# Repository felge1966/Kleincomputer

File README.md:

# Projekte um die DDR Kleincomputer 
- KC85/2...85/5
- Z9001, KC85/1 und KC87 
- MRB Z1013
- AC1 (org / AC1-2010 / Neubauprojekt AC1-2017 /AC1Pico)
- Polycomputer Poly880
- LC80 (LC80 org. / LC80ex)

## Dev Software:
 - WinCupl
 - Kicad 5.1

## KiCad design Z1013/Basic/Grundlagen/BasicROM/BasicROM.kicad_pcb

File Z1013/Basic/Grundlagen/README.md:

# Z1013-Basic
Platinenprojekt Z1013 Basicerweiterung

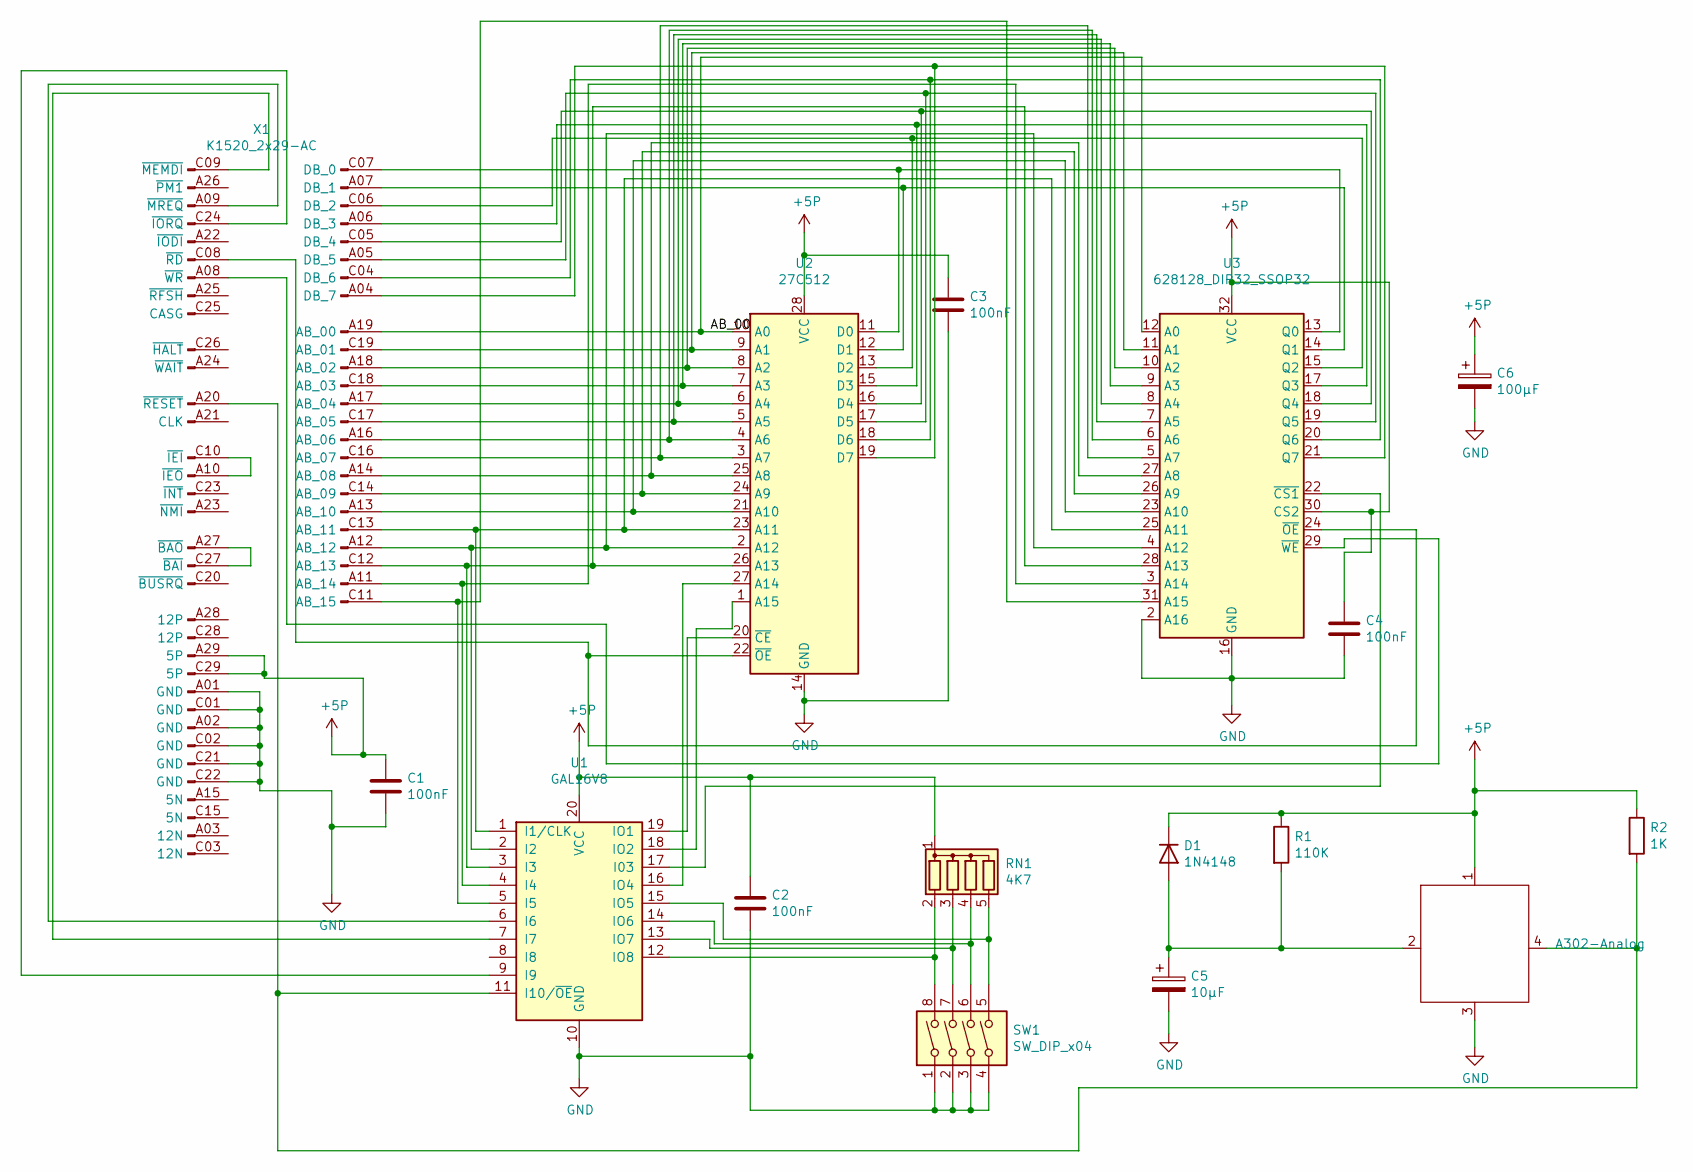
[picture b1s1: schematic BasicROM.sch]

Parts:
C1, C2, C3, C4: 100nF; C_Axial_L3.8mm_D2.6mm_P10.00mm_Horizontal
C5: 10µF; CP_Radial_D6.3mm_P2.50mm
C6: 100µF; CP_Axial_L18.0mm_D8.0mm_P25.00mm_Horizontal
D1: 1N4148; D_DO-35_SOD27_P7.62mm_Horizontal
R1: 110K; R_Axial_DIN0207_L6.3mm_D2.5mm_P7.62mm_Horizontal
R2: 1K; R_Axial_DIN0207_L6.3mm_D2.5mm_P7.62mm_Horizontal
RN1: 4K7; R_Array_SIP5
SW1: SW_DIP_x04; SW_DIP_SPSTx04_Piano_10.8x11.72mm_W7.62mm_P2.54mm
U1: GAL16V8; DIP-20_W7.62mm
U2: 27C512; DIP-28_W15.24mm
U3: 628128_DIP32_SSOP32; DIP-32_W15.24mm
U4: A302-Analog; DIP-4_W7.62mm
X1: K1520_2x29-AC; K1520_EFS2x29_DIN_male

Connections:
+5P: C1.1, C2.1, C3.1, C4.1, C6.1, D1.1 (K), R1.1, R2.1, RN1.1 (common), U1.20 (VCC), U2.28 (VCC), U3.30 (CS2), U3.32 (VCC), U4.1, X1.A29 (5P), X1.C29 (5P)
/AB_00: U2.10 (A0), U3.12 (A0), X1.A19 (AB_00)
GND: C1.2, C2.2, C3.2, C4.2, C5.2, C6.2, SW1.1, SW1.2, SW1.3, SW1.4, U1.10 (GND), U2.14 (GND), U3.2 (A16), U3.16 (GND), U4.3, X1.A01 (GND), X1.A02 (GND), X1.C01 (GND), X1.C02 (GND), X1.C21 (GND), X1.C22 (GND)
unnamed: C5.1, D1.2 (A), R1.2, U4.2
unnamed: R2.2, U1.11 (I10/~OE~), U4.4, X1.A20 (~RESET)
unnamed: RN1.2 (R1), SW1.8, U1.12 (IO8)
unnamed: RN1.3 (R2), SW1.7, U1.13 (IO7)
unnamed: RN1.4 (R3), SW1.6, U1.14 (IO6)
unnamed: RN1.5 (R4), SW1.5, U1.15 (IO5)
unnamed: U1.1 (I1/CLK), U2.23 (A11), U3.25 (A11), X1.C13 (AB_11)
unnamed: U1.2 (I2), U2.2 (A12), U3.4 (A12), X1.A12 (AB_12)
unnamed: U1.3 (I3), U2.26 (A13), U3.28 (A13), X1.C12 (AB_13)
unnamed: U1.4 (I4), U3.3 (A14), X1.A11 (AB_14)
unnamed: U1.5 (I5), U3.31 (A15), X1.C11 (AB_15)
unnamed: U1.6 (I6), X1.A09 (~MREQ)
unnamed: U1.7 (I7), X1.C09 (~MEMDI)
unnamed: U1.9 (I9), X1.C24 (~IORQ)
unnamed: U1.16 (IO4), U2.27 (A14)
unnamed: U1.17 (I03), U3.22 (~CS1)
unnamed: U1.18 (IO2), U2.1 (A15)
unnamed: U1.19 (IO1), U2.20 (~CE)
unnamed: U2.3 (A7), U3.5 (A7), X1.C16 (AB_07)
unnamed: U2.4 (A6), U3.6 (A6), X1.A16 (AB_06)
unnamed: U2.5 (A5), U3.7 (A5), X1.C17 (AB_05)
unnamed: U2.6 (A4), U3.8 (A4), X1.A17 (AB_04)
unnamed: U2.7 (A3), U3.9 (A3), X1.C18 (AB_03)
unnamed: U2.8 (A2), U3.10 (A2), X1.A18 (AB_02)
unnamed: U2.9 (A1), U3.11 (A1), X1.C19 (AB_01)
unnamed: U2.11 (D0), U3.13 (Q0), X1.C07 (DB_0)
unnamed: U2.12 (D1), U3.14 (Q1), X1.A07 (DB_1)
unnamed: U2.13 (D2), U3.15 (Q2), X1.C06 (DB_2)
unnamed: U2.15 (D3), U3.17 (Q3), X1.A06 (DB_3)
unnamed: U2.16 (D4), U3.18 (Q4), X1.C05 (DB_4)
unnamed: U2.17 (D5), U3.19 (Q5), X1.A05 (DB_5)
unnamed: U2.18 (D6), U3.20 (Q6), X1.C04 (DB_6)
unnamed: U2.19 (D7), U3.21 (Q7), X1.A04 (DB_7)
unnamed: U2.21 (A10), U3.23 (A10), X1.A13 (AB_10)
unnamed: U2.22 (~OE), U3.24 (~OE), X1.C08 (~RD)
unnamed: U2.24 (A9), U3.26 (A9), X1.C14 (AB_09)
unnamed: U2.25 (A8), U3.27 (A8), X1.A14 (AB_08)
unnamed: U3.29 (~WE), X1.A08 (~WR)
unnamed: X1.A10 (~IEO), X1.C10 (~IEI)
unnamed: X1.A27 (~BAO), X1.C27 (~BAI)

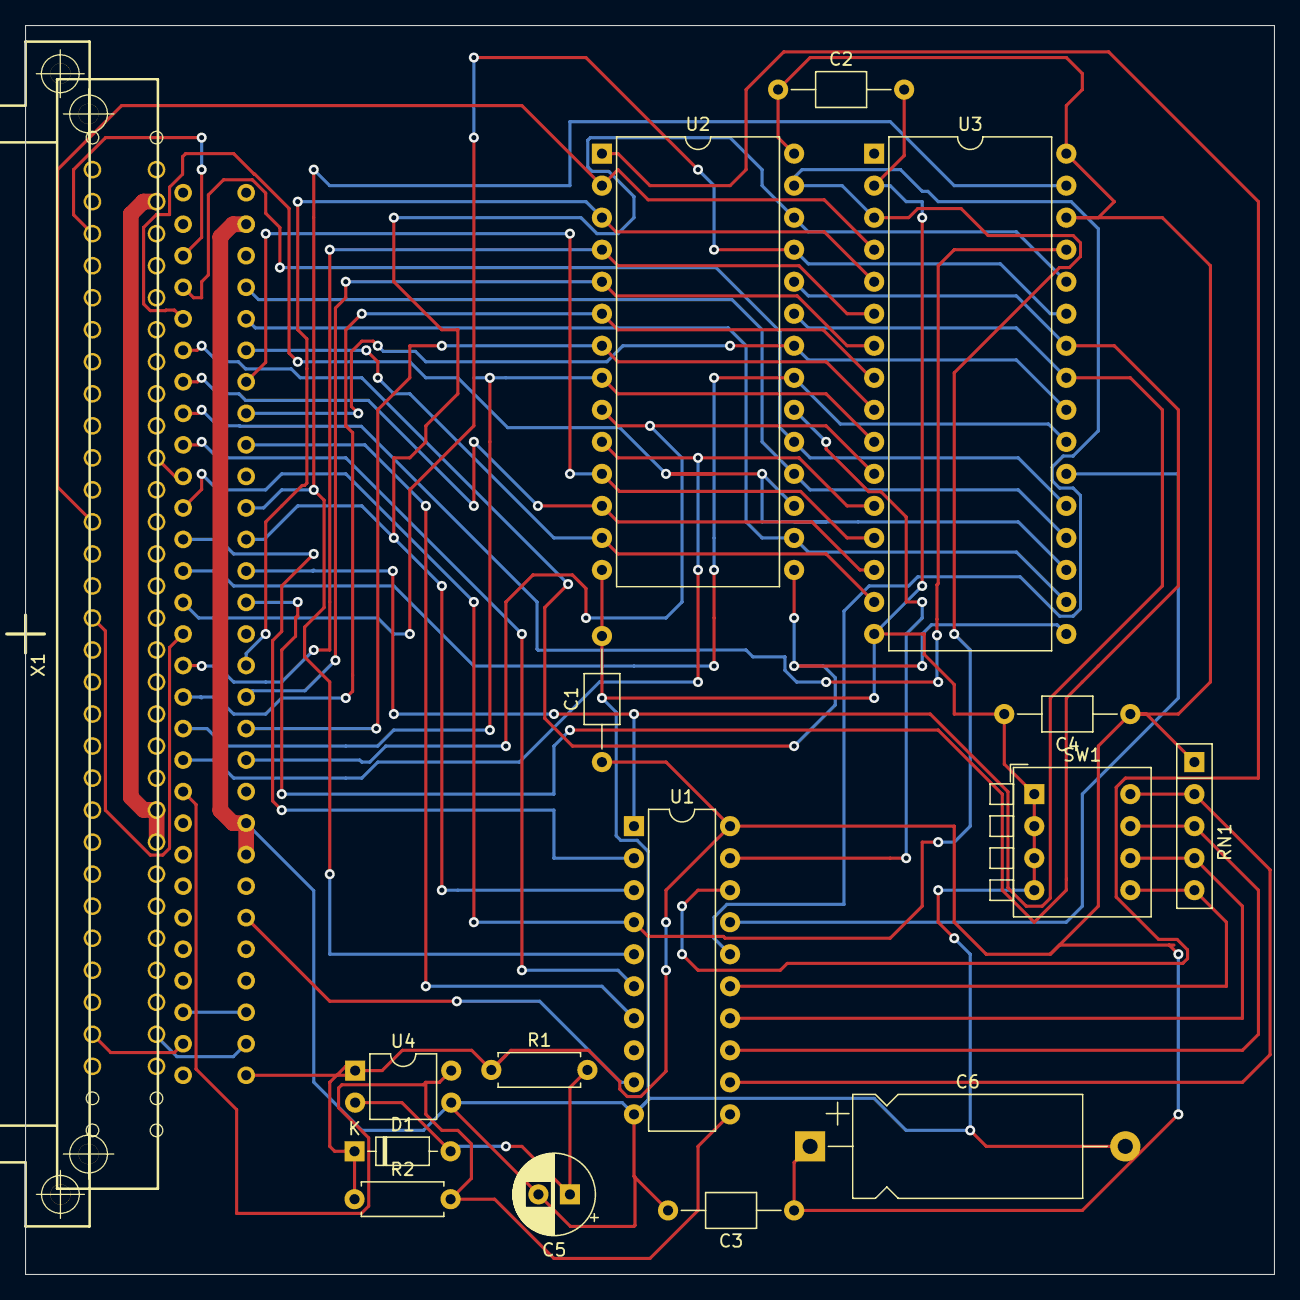
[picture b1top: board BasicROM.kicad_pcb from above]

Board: 2 copper layers, 99.1 x 99.1 mm, 16 parts (0 on the bottom side), 43 nets.

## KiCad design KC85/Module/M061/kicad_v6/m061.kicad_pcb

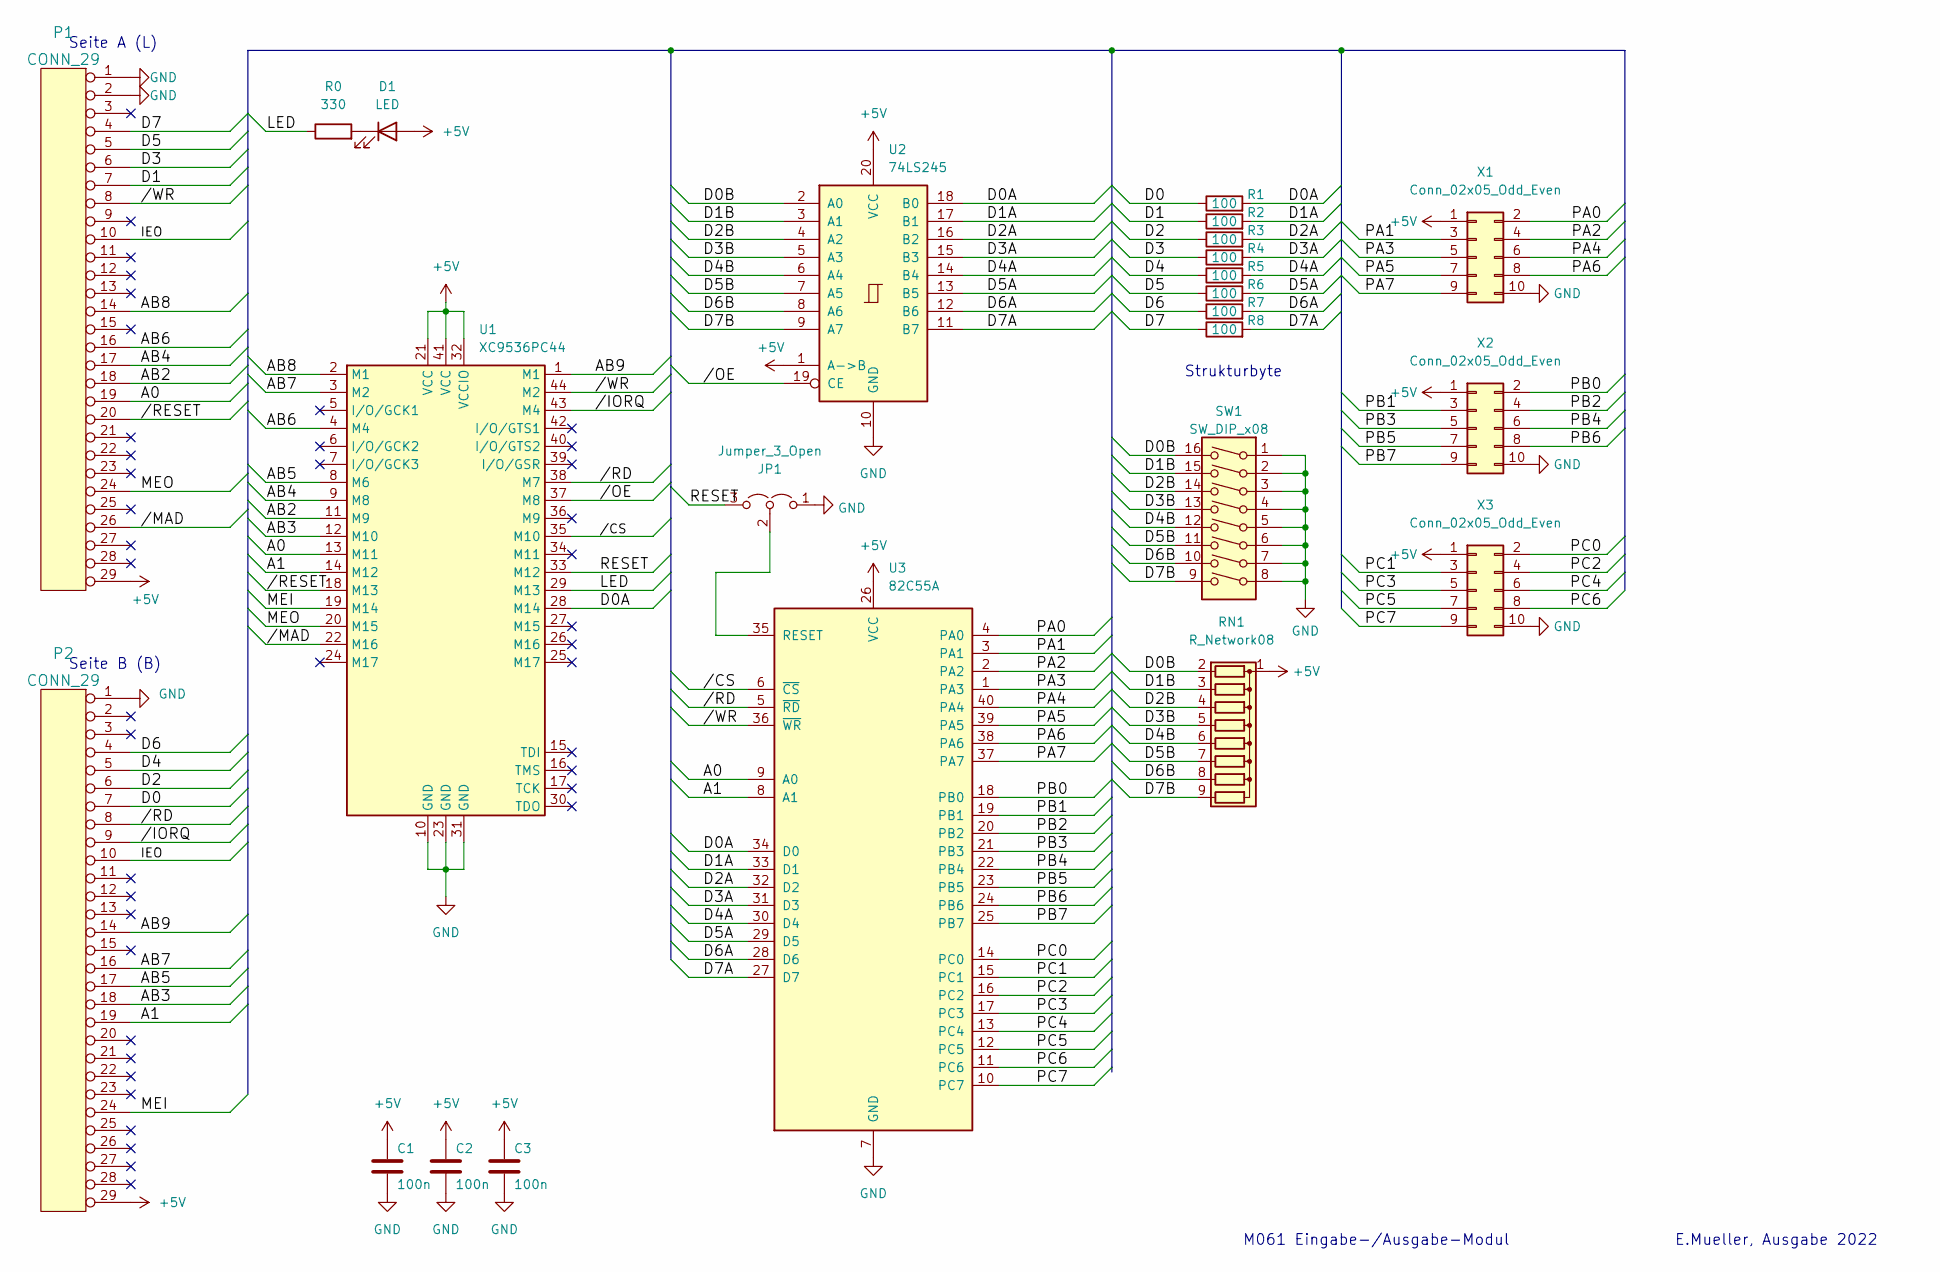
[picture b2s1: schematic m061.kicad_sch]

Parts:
C1, C2, C3: 100n; C_Disc_D7.5mm_W2.5mm_P5.00mm
D1: LED; LED_D5.0mm_Horizontal_O6.35mm_Z3.0mm
JP1: Jumper_3_Open; PinHeader_1x03_P2.54mm_Vertical
P1: CONN_29; KAMM_LEITER
P2: CONN_29; KAMM_BESTUECK
R0: 330; R_Axial_DIN0207_L6.3mm_D2.5mm_P10.16mm_Horizontal
R1, R2, R3, R4, R5, R6, R7, R8: 100; R_Axial_DIN0207_L6.3mm_D2.5mm_P10.16mm_Horizontal
RN1: R_Network08; R_Array_SIP9
SW1: SW_DIP_x08; SW_DIP_SPSTx08_Slide_9.78x22.5mm_W7.62mm_P2.54mm
U1: XC9536PC44; PLCC-44_THT-Socket
U2: 74LS245; DIP-20_W7.62mm
U3: 82C55A; DIP-40_W15.24mm
X1, X2, X3: Conn_02x05_Odd_Even; PinHeader_2x05_P2.54mm_Vertical

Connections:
+5V: C1.1, C2.1, C3.1, D1.2 (A), P1.29, P2.29, RN1.1 (common), U1.21 (VCC), U1.32 (VCCIO), U1.41 (VCC), U2.1 (A->B), U2.20 (VCC), U3.26 (VCC), X1.1, X2.1, X3.1
/A0: P1.19, U1.13 (M11), U3.9 (A0)
/A1: P2.19, U1.14 (M12), U3.8 (A1)
/AB2: P1.18, U1.11 (M9)
/AB3: P2.18, U1.12 (M10)
/AB4: P1.17, U1.9 (M8)
/AB5: P2.17, U1.8 (M6)
/AB6: P1.16, U1.4 (M4)
/AB7: P2.16, U1.3 (M2)
/AB8: P1.14, U1.2 (M1)
/AB9: P2.14, U1.1 (M1)
/D0: P2.7, R1.1
/D0A: R1.2, U1.28 (M14), U2.18 (B0), U3.34 (D0)
/D0B: RN1.2 (R1), SW1.16, U2.2 (A0)
/D1: P1.7, R2.1
/D1A: R2.2, U2.17 (B1), U3.33 (D1)
/D1B: RN1.3 (R2), SW1.15, U2.3 (A1)
/D2: P2.6, R3.1
/D2A: R3.2, U2.16 (B2), U3.32 (D2)
/D2B: RN1.4 (R3), SW1.14, U2.4 (A2)
/D3: P1.6, R4.1
/D3A: R4.2, U2.15 (B3), U3.31 (D3)
/D3B: RN1.5 (R4), SW1.13, U2.5 (A3)
/D4: P2.5, R5.1
/D4A: R5.2, U2.14 (B4), U3.30 (D4)
/D4B: RN1.6 (R5), SW1.12, U2.6 (A4)
/D5: P1.5, R6.1
/D5A: R6.2, U2.13 (B5), U3.29 (D5)
/D5B: RN1.7 (R6), SW1.11, U2.7 (A5)
/D6: P2.4, R7.1
/D6A: R7.2, U2.12 (B6), U3.28 (D6)
/D6B: RN1.8 (R7), SW1.10, U2.8 (A6)
/D7: P1.4, R8.1
/D7A: R8.2, U2.11 (B7), U3.27 (D7)
/D7B: RN1.9 (R8), SW1.9, U2.9 (A7)
/IEO: P1.10, P2.10
/LED: R0.1, U1.29 (M13)
/MEI: P2.24, U1.19 (M14)
/MEO: P1.24, U1.20 (M15)
/PA0: U3.4 (PA0), X1.2
/PA1: U3.3 (PA1), X1.3
/PA2: U3.2 (PA2), X1.4
/PA3: U3.1 (PA3), X1.5
/PA4: U3.40 (PA4), X1.6
/PA5: U3.39 (PA5), X1.7
/PA6: U3.38 (PA6), X1.8
/PA7: U3.37 (PA7), X1.9
/PB0: U3.18 (PB0), X2.2
/PB1: U3.19 (PB1), X2.3
/PB2: U3.20 (PB2), X2.4
/PB3: U3.21 (PB3), X2.5
/PB4: U3.22 (PB4), X2.6
/PB5: U3.23 (PB5), X2.7
/PB6: U3.24 (PB6), X2.8
/PB7: U3.25 (PB7), X2.9
/PC0: U3.14 (PC0), X3.2
/PC1: U3.15 (PC1), X3.3
/PC2: U3.16 (PC2), X3.4
/PC3: U3.17 (PC3), X3.5
/PC4: U3.13 (PC4), X3.6
/PC5: U3.12 (PC5), X3.7
/PC6: U3.11 (PC6), X3.8
/PC7: U3.10 (PC7), X3.9
/RESET: JP1.3 (B), U1.33 (M12)
//CS: U1.35 (M10), U3.6 (~CS)
//MAD: P1.26, U1.22 (M16)
//OE: U1.37 (M8), U2.19 (CE)
//RESET: P1.20, U1.18 (M13)
GND: C1.2, C2.2, C3.2, JP1.1 (A), P1.1, P1.2, P2.1, SW1.1, SW1.2, SW1.3, SW1.4, SW1.5, SW1.6, SW1.7, SW1.8, U1.10 (GND), U1.23 (GND), U1.31 (GND), U2.10 (GND), U3.7 (GND), X1.10, X2.10, X3.10
unnamed: D1.1 (K), R0.2
unnamed: JP1.2 (C), U3.35 (RESET)

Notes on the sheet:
E.Mueller, Ausgabe 2022
Seite B (B)
M061 Eingabe-/Ausgabe-Modul
Strukturbyte
Seite A (L)

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
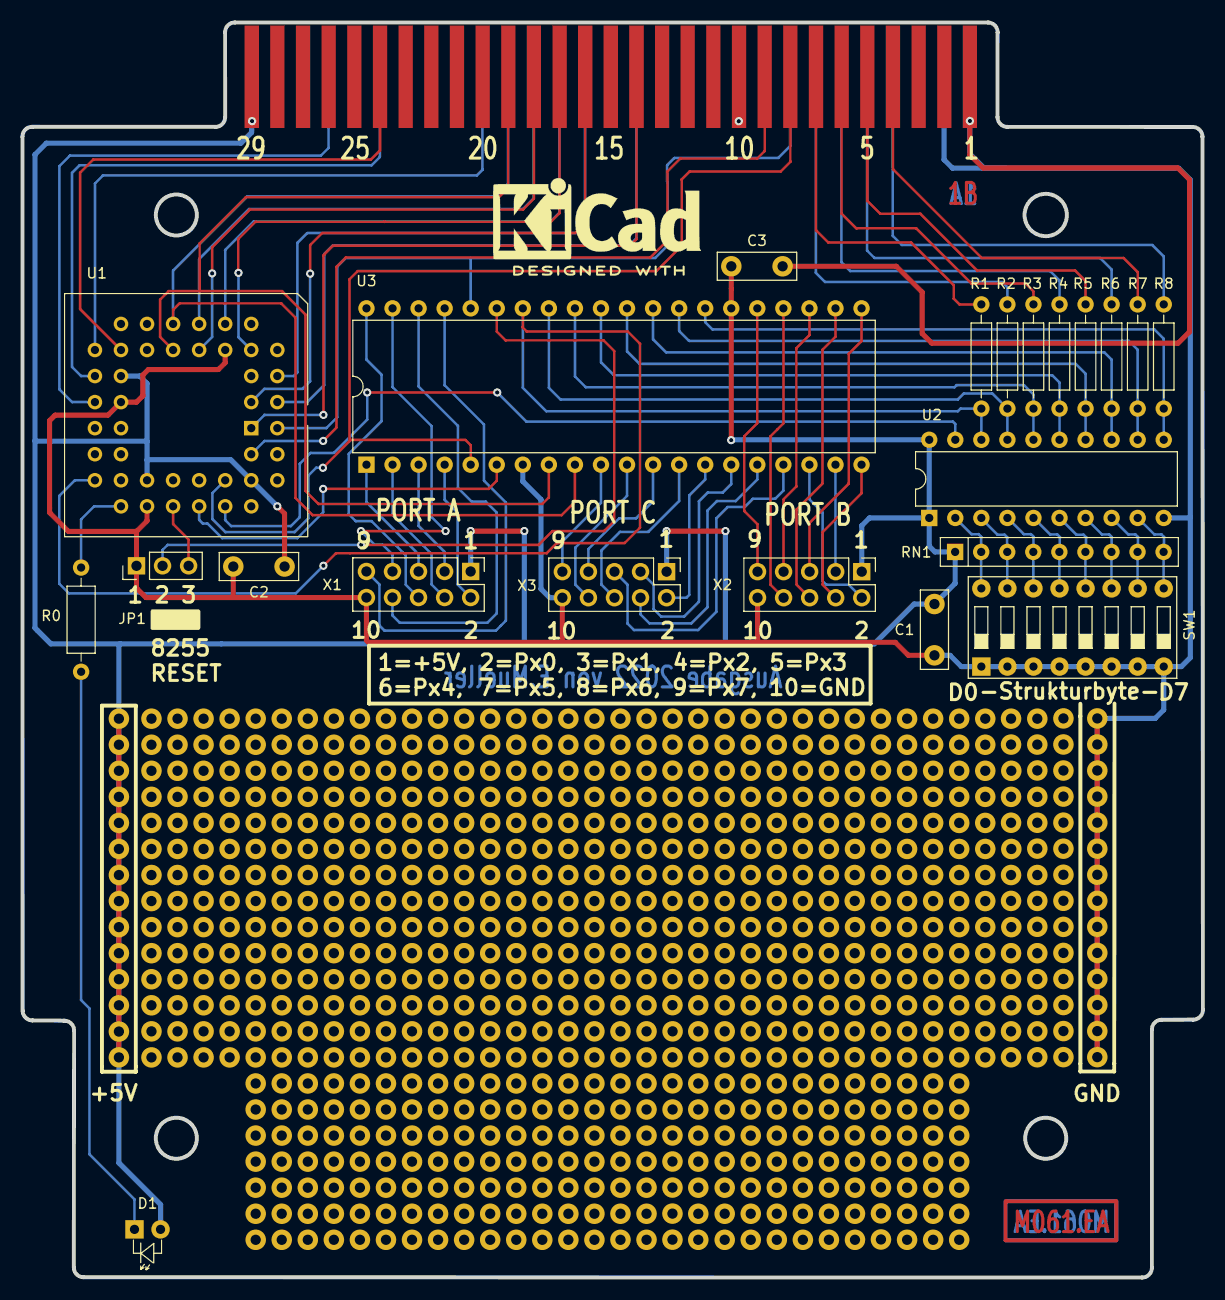
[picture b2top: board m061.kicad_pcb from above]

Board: 2 copper layers, 115.1 x 122.3 mm, 24 parts (0 on the bottom side), 74 nets.

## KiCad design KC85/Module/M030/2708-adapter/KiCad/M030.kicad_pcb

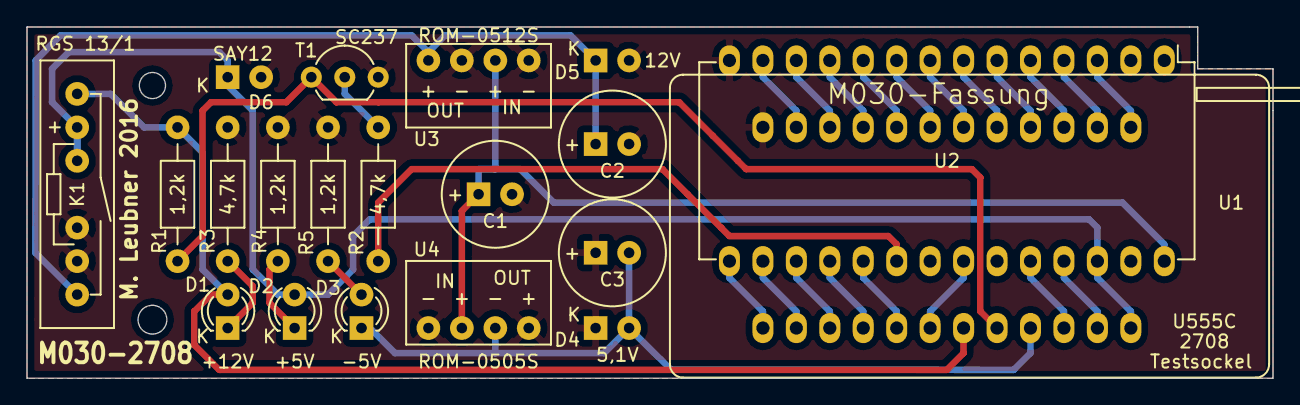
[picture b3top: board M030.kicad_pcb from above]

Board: 2 copper layers, 94.6 x 26.7 mm, 20 parts (0 on the bottom side), 31 nets.

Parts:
C1, C2, C3: 10µ; C1V8
D1: +12V; LED-3MM
D2: +5V; LED-3MM
D3: -5V; LED-3MM
D4: 5,1V; Diode_DO-41_SOD81_Vertical_KathodeUp
D5: 12V; Diode_DO-41_SOD81_Vertical_KathodeUp
D6: SAY12; Diode_DO-41_SOD81_Vertical_AnodeUp
K1: RGS 13/1; RGS13
R1, R4, R5: 1,2k; Resistor_Horizontal_RM10mm
R2, R3: 4,7k; Resistor_Horizontal_RM10mm
T1: SC237; TO-92_Inline_Wide
U1: M030-Fassung; DIP-28_W15.24mm_LongPads
U2: U555C; DIP-24_Testsockel
U3: ROM-0512S; DCDC
U4: ROM-0505S; DCDC

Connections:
-: D2.2, D6.1, K1.2, K1.3, U1.26, U2.24
/+12V: C2.1, D5.1, K1.7, U3.4
/-5V: C3.2, D3.1, D4.2, U2.21, U4.3
//CE: R2.1, U1.20
/A0: U1.10, U2.8
/A1: U1.9, U2.7
/A2: U1.8, U2.6
/A3: U1.7, U2.5
/A4: U1.6, U2.4
/A5: U1.5, U2.3
/A6: U1.4, U2.2
/A7: U1.3, U2.1
/A8: U1.25, U2.23
/A9: U1.24, U2.22
/CS/WE: R1.2, T1.1, U2.20
/D0: U1.11, U2.9
/D1: U1.12, U2.10
/D2: U1.13, U2.11
/D3: U1.15, U2.13
/D4: U1.16, U2.14
/D5: U1.17, U2.15
/D6: U1.18, U2.16
/D7: U1.19, U2.17
/PR: U1.22, U2.18
/Udd: D1.2, K1.1, R1.1, U2.19
/Vcc: C1.1, U1.28, U3.2, U4.2
GND: C1.2, C2.2, C3.1, D4.1, D5.2, D6.2, K1.5, K1.6, R3.2, R4.2, R5.2, T1.3, U1.14, U2.12, U3.1, U3.3, U4.1, U4.4
unnamed: D1.1, R3.1
unnamed: D2.1, R4.1
unnamed: D3.2, R5.1
unnamed: R2.2, T1.2

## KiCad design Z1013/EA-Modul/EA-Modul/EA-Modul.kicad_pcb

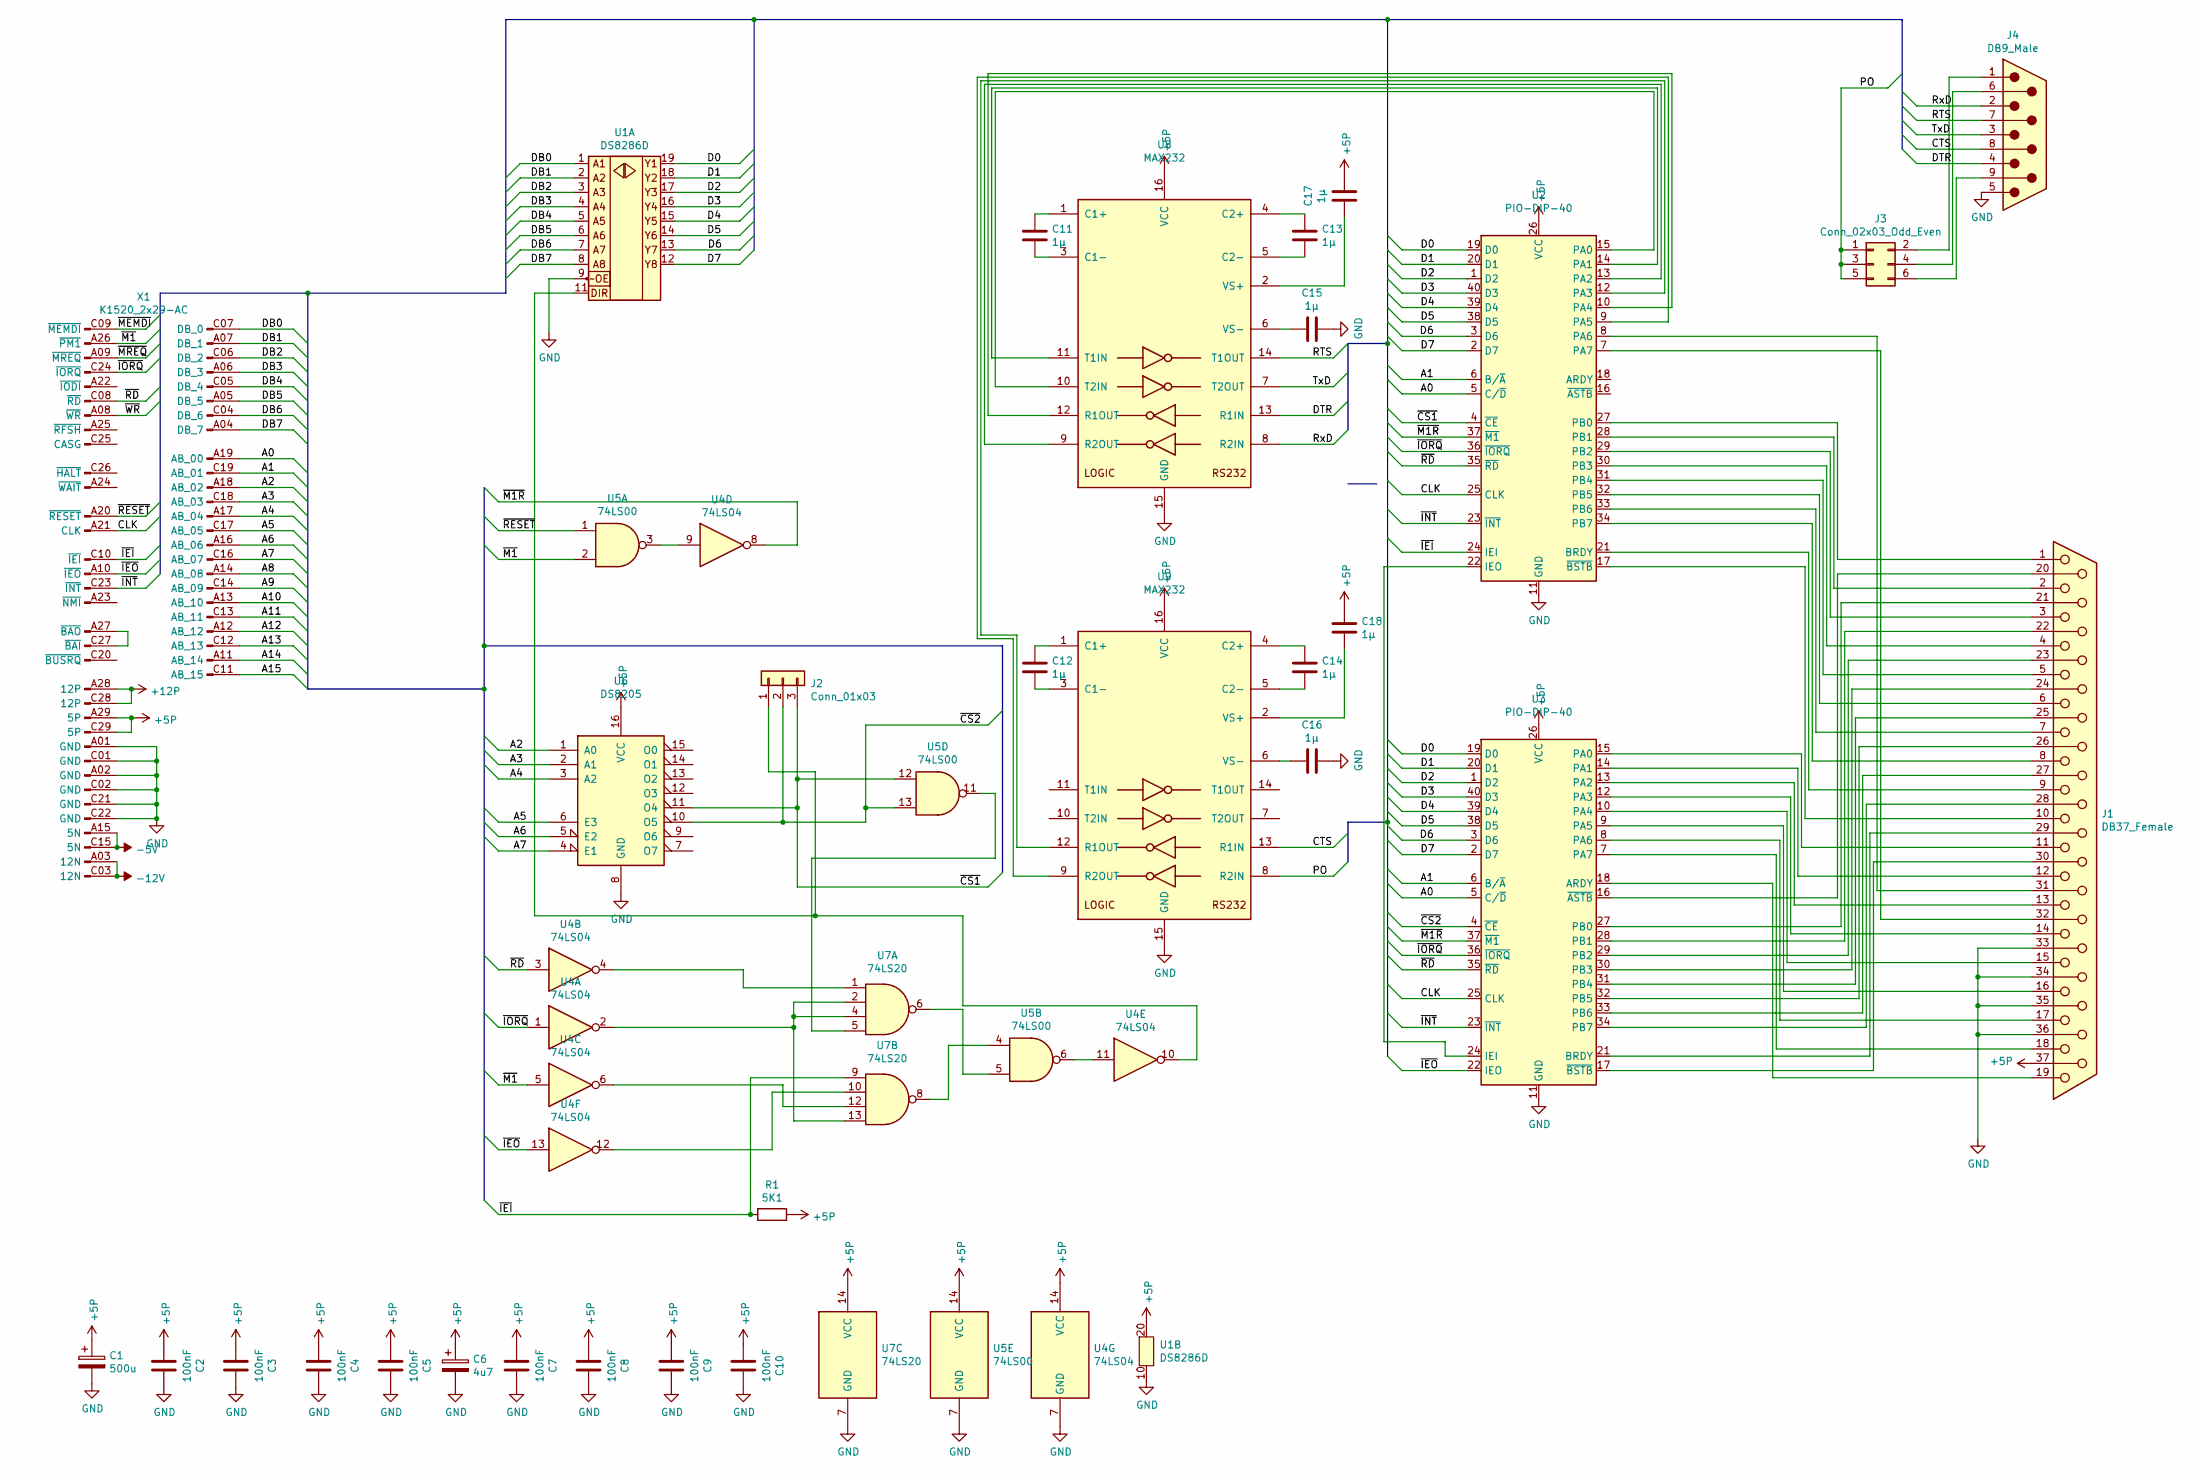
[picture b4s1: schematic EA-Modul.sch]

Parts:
C1: 500u; CP_Radial_D8.0mm_P3.80mm
C2, C3, C4, C5, C7, C8, C9, C10: 100nF; C_Disc_D3.0mm_W2.0mm_P2.50mm
C6: 4u7; CP_Radial_D5.0mm_P2.50mm
C11, C12, C13, C14, C15, C16, C17, C18: 1µ; C_Disc_D3.0mm_W2.0mm_P2.50mm
J1: DB37_Female; DSUB-37_Female_Horizontal_P2.77x2.84mm_EdgePinOffset4.94mm_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
J2: Conn_01x03; PinHeader_1x03_P2.54mm_Vertical
J3: Conn_02x03_Odd_Even; PinHeader_2x03_P2.54mm_Vertical
J4: DB9_Male; DSUB-9_Male_Horizontal_P2.77x2.84mm_EdgePinOffset4.94mm_Hou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
R1: 5K1; R_Axial_DIN0207_L6.3mm_D2.5mm_P10.16mm_Horizontal
U1: DS8286D; DIP-20_W7.62mm_LongPads
U2, U3: PIO-DIP-40; DIP-40_W15.24mm
U4: 74LS04
U5: 74LS00
U6: DS8205; DIP-16_W7.62mm_LongPads
U7: 74LS20; DIP-14_W7.62mm_LongPads
U8, U9: MAX232; DIP-16_W7.62mm_LongPads
X1: K1520_2x29-AC; K1520_EFS2x29_DIN_male

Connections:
+5P: C1.1, C2.2, C3.2, C4.2, C5.2, C6.1, C7.2, C8.2, C9.2, C10.2, C17.1, C18.1, J1.37, R1.1, U1.20 (Vcc), U2.26 (VCC), U3.26 (VCC), U4.14 (VCC), U5.14 (VCC), U6.16 (VCC), U7.14 (VCC), U8.16 (VCC), U9.16 (VCC), X1.A29 (5P), X1.C29 (5P)
+12P: X1.A28 (12P), X1.C28 (12P)
-5V: X1.A15 (5N), X1.C15 (5N)
-12V: X1.A03 (12N), X1.C03 (12N)
/A0: U2.5 (C/~D~), U3.5 (C/~D~), X1.A19 (AB_00)
/A1: U2.6 (B/~A~), U3.6 (B/~A~), X1.C19 (AB_01)
/A2: U6.1 (A0), X1.A18 (AB_02)
/A3: U6.2 (A1), X1.C18 (AB_03)
/A4: U6.3 (A2), X1.A17 (AB_04)
/A5: U6.6 (E3), X1.C17 (AB_05)
/A6: U6.5 (E2), X1.A16 (AB_06)
/A7: U6.4 (E1), X1.C16 (AB_07)
/A8: X1.A14 (AB_08)
/A9: X1.C14 (AB_09)
/A10: X1.A13 (AB_10)
/A11: X1.C13 (AB_11)
/A12: X1.A12 (AB_12)
/A13: X1.C12 (AB_13)
/A14: X1.A11 (AB_14)
/A15: X1.C11 (AB_15)
/CLK: U2.25 (CLK), U3.25 (CLK), X1.A21 (CLK)
/CTS: J4.8, U9.13 (R1IN)
/D0: U1.19 (Y1), U2.19 (D0), U3.19 (D0)
/D1: U1.18 (Y2), U2.20 (D1), U3.20 (D1)
/D2: U1.17 (Y3), U2.1 (D2), U3.1 (D2)
/D3: U1.16 (A4), U2.40 (D3), U3.40 (D3)
/D4: U1.15 (Y5), U2.39 (D4), U3.39 (D4)
/D5: U1.14 (Y6), U2.38 (D5), U3.38 (D5)
/D6: U1.13 (Y7), U2.3 (D6), U3.3 (D6)
/D7: U1.12 (Y8), U2.2 (D7), U3.2 (D7)
/DB0: U1.1 (A1), X1.C07 (DB_0)
/DB1: U1.2 (A2), X1.A07 (DB_1)
/DB2: U1.3 (A3), X1.C06 (DB_2)
/DB3: U1.4 (A4), X1.A06 (DB_3)
/DB4: U1.5 (A5), X1.C05 (DB_4)
/DB5: U1.6 (A6), X1.A05 (DB_5)
/DB6: U1.7 (A7), X1.C04 (DB_6)
/DB7: U1.8 (A8), X1.A04 (DB_7)
/DTR: J4.4, U8.13 (R1IN)
/PO: J3.1, J3.3, J3.5, U9.8 (R2IN)
/RTS: J4.7, U8.14 (T1OUT)
/RxD: J4.2, U8.8 (R2IN)
/TxD: J4.3, U8.7 (T2OUT)
/~CS1: J2.3, U2.4 (~CE~), U5.12, U6.11 (O4)
/~CS2: J2.2, U3.4 (~CE~), U5.13, U6.10 (O5)
/~IEI: R1.2, U2.24 (IEI), U7.9, X1.C10 (~IEI)
/~IEO: U3.22 (IEO), U4.13, X1.A10 (~IEO)
/~INT: U2.23 (~INT~), U3.23 (~INT~), X1.C23 (~INT)
/~IORQ: U2.36 (~IORQ~), U3.36 (~IORQ~), U4.1, X1.C24 (~IORQ)
/~M1: U4.5, U5.2, X1.A26 (~PM1)
/~M1R: U2.37 (~M1~), U3.37 (~M1~), U4.8
/~MEMDI: X1.C09 (~MEMDI)
/~MREQ: X1.A09 (~MREQ)
/~RD: U2.35 (~RD~), U3.35 (~RD~), U4.3, X1.C08 (~RD)
/~RESET: U5.1, X1.A20 (~RESET)
/~WR: X1.A08 (~WR)
GND: C1.2, C2.1, C3.1, C4.1, C5.1, C6.2, C7.1, C8.1, C9.1, C10.1, C15.1, C16.1, J1.33, J1.34, J1.35, J1.36, J4.5, U1.9 (~OE), U1.10 (GND), U2.11 (GND), U3.11 (GND), U4.7 (GND), U5.7 (GND), U6.8 (GND), U7.7 (GND), U8.15 (GND), U9.15 (GND), X1.A01 (GND), X1.A02 (GND), X1.C01 (GND), X1.C02 (GND), X1.C21 (GND), X1.C22 (GND)
unnamed: C11.1, U8.1 (C1+)
unnamed: C11.2, U8.3 (C1-)
unnamed: C12.1, U9.1 (C1+)
unnamed: C12.2, U9.3 (C1-)
unnamed: C13.1, U8.4 (C2+)
unnamed: C13.2, U8.5 (C2-)
unnamed: C14.1, U9.4 (C2+)
unnamed: C14.2, U9.5 (C2-)
unnamed: C15.2, U8.6 (VS-)
unnamed: C16.2, U9.6 (VS-)
unnamed: C17.2, U8.2 (VS+)
unnamed: C18.2, U9.2 (VS+)
unnamed: J1.1, U2.27 (PB0)
unnamed: J1.2, U2.28 (PB1)
unnamed: J1.3, U2.29 (PB2)
unnamed: J1.4, U2.30 (PB3)
unnamed: J1.5, U2.31 (PB4)
unnamed: J1.6, U2.32 (PB5)
unnamed: J1.7, U2.33 (PB6)
unnamed: J1.8, U2.34 (PB7)
unnamed: J1.9, U2.21 (BRDY)
unnamed: J1.10, U2.17 (~BSTB~)
unnamed: J1.11, U3.15 (PA0)
unnamed: J1.12, U3.14 (PA1)
unnamed: J1.13, U3.13 (PA2)
unnamed: J1.14, U3.12 (PA3)
unnamed: J1.15, U3.10 (PA4)
unnamed: J1.16, U3.9 (PA5)
unnamed: J1.17, U3.8 (PA6)
unnamed: J1.18, U3.7 (PA7)
unnamed: J1.19, U3.18 (ARDY)
unnamed: J1.20, U3.16 (~ASTB~)
unnamed: J1.21, U3.27 (PB0)
unnamed: J1.22, U3.28 (PB1)
unnamed: J1.23, U3.29 (PB2)
unnamed: J1.24, U3.30 (PB3)
unnamed: J1.25, U3.31 (PB4)
unnamed: J1.26, U3.32 (PB5)
unnamed: J1.27, U3.33 (PB6)
unnamed: J1.28, U3.34 (PB7)
unnamed: J1.29, U3.21 (BRDY)
unnamed: J1.30, U3.17 (~BSTB~)
unnamed: J1.31, U2.8 (PA6)
unnamed: J1.32, U2.7 (PA7)
unnamed: J2.1, U1.11 (STB), U4.10
unnamed: J3.2, J4.1
unnamed: J3.4, J4.6
unnamed: J3.6, J4.9
unnamed: U2.9 (PA5), U9.9 (R2OUT)
unnamed: U2.10 (PA4), U8.12 (R1OUT)
unnamed: U2.12 (PA3), U9.12 (R1OUT)
unnamed: U2.13 (PA2), U8.9 (R2OUT)
unnamed: U2.14 (PA1), U8.11 (T1IN)
unnamed: U2.15 (PA0), U8.10 (T2IN)
unnamed: U2.22 (IEO), U3.24 (IEI)
unnamed: U4.2, U7.2, U7.4, U7.13
unnamed: U4.4, U7.1
unnamed: U4.6, U7.12
unnamed: U4.9, U5.3
unnamed: U4.11, U5.6
unnamed: U4.12, U7.10
unnamed: U5.4, U7.8
unnamed: U5.5, U7.6
unnamed: U5.11, U7.5
unnamed: X1.A27 (~BAO), X1.C27 (~BAI)

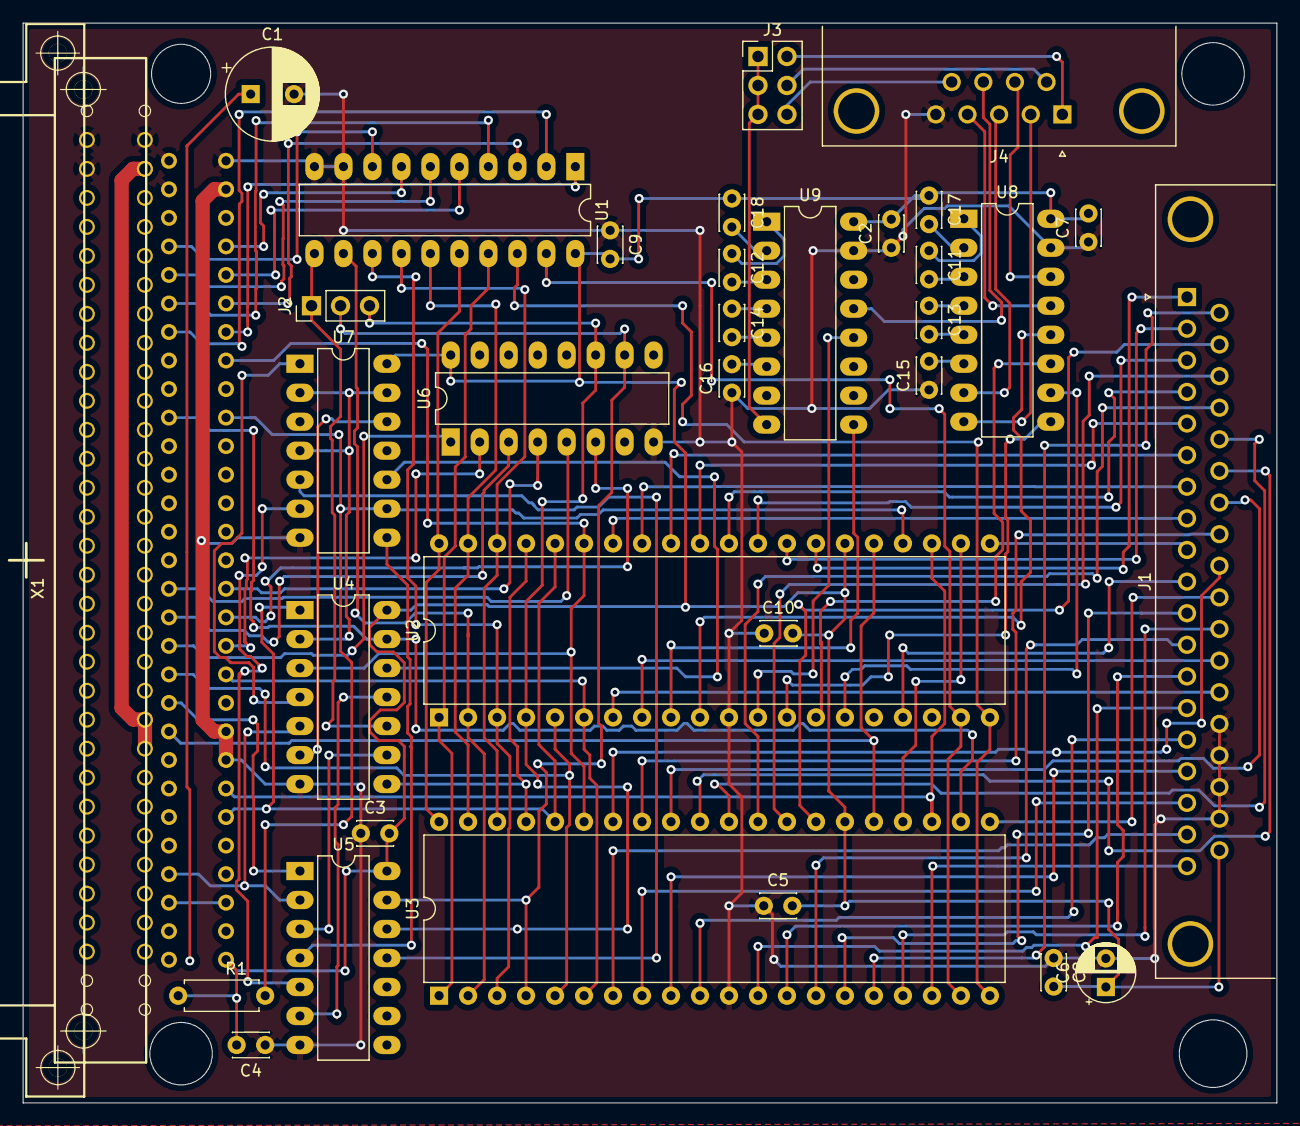
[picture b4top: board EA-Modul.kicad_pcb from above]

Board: 2 copper layers, 109.9 x 94.6 mm, 33 parts (0 on the bottom side), 111 nets.
